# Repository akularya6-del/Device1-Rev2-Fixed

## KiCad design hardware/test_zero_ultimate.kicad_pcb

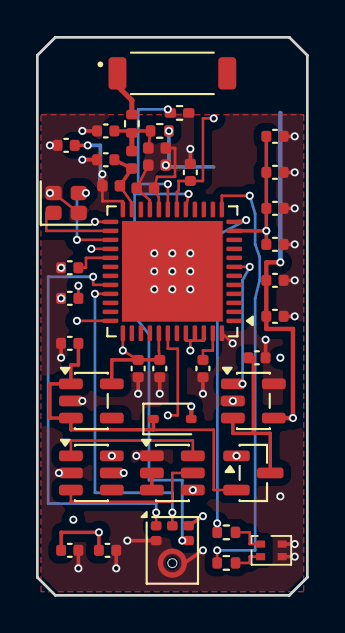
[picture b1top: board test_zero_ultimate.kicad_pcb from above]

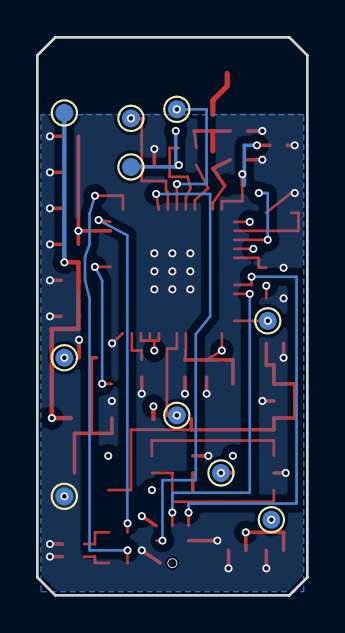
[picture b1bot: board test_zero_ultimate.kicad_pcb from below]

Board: 4 copper layers, 15.0 x 31.0 mm, 50 parts (10 on the bottom side), 33 nets.

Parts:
ANT1: 0868AT43A0020E; Johanson_0868AT43A0020E_CUSTOM
C1, C2, C3, C4, C5, C7, C8, C9, C10, C11, C12, C13, C14, C15, C16, C17, C18, C20, C21: C_0402_1005Metric
C22, C23: 1.5pF; C_0402_1005Metric
D1: D_SOD-323
D2: LED_LiteOn_LTST-C295K_1.6x0.8mm
L1: L_0402_1005Metric
L2: 47nH; L_0402_1005Metric
L3: 18nH; L_0402_1005Metric
MK1: Knowles_SPH0645LM4H-6_3.5x2.65mm
Q1: SOT-23-6
Q2: SOT-23
R1, R6, R7: R_0402_1005Metric
R_ANT: R_0402_1005Metric
R_TEST: R_0402_1005Metric
TP_3V3: TestPoint_Pad_D1.0mm
TP_BATT_N: TestPoint_Pad_D1.0mm
TP_BATT_P: TestPoint_Pad_D1.0mm
TP_BOOT0: TestPoint_Pad_D1.0mm
TP_GND: TestPoint_Pad_D1.0mm
TP_NRST: TestPoint_Pad_D1.0mm
TP_RF: TestPoint_Pad_D1.0mm
TP_SWCLK: TestPoint_Pad_D1.0mm
TP_SWDIO: TestPoint_Pad_D1.0mm
TP_VBUS: TestPoint_Pad_D1.0mm
U1: QFN-48-1EP_7x7mm_P0.5mm_EP5.6x5.6mm
U2, U5: SOT-23-5
U4: SOT-23-6
Y1: Crystal_SMD_2016-4Pin_2.0x1.6mm

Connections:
/3V3: C1.1, C2.1, C3.1, C5.1, C8.1, C15.1, C16.1, C20.1, C21.1, MK1.5, TP_3V3.1, U1.11, U1.25, U1.28, U1.37, U1.41, U1.44, U1.45, U1.46, U5.5
/ANT_FEED: ANT1.1, R_ANT.2
/BATT_NEG: Q1.4, TP_BATT_N.1, U4.6
/BATT_POS: TP_BATT_P.1, U4.5
/BOOT0: R1.1, TP_BOOT0.1, U1.19
/CHG_STAT: U1.7, U2.1
/GATE_OC: Q1.5, U4.3
/GATE_OD: Q1.6, U4.1
/GND: C1.2, C2.2, C3.2, C4.2, C5.2, C7.2, C8.2, C9.2, C10.2, C11.2, C12.2, C13.2, C14.2, C15.2, C16.2, C17.2, C18.2, C20.2, C21.2, C23.2, D2.3, D2.4, MK1.2, MK1.3, Q1.1, R1.2, TP_GND.1, U1.48, U1.49, U2.2, U2.5, U4.2, U5.2, Y1.2, Y1.4
/LED_B: D2.2, R7.2
/LED_B_DRV: R7.1, U1.13
/LED_R: D2.1, R6.2
/LED_R_DRV: R6.1, U1.12
/MIC_SCK: MK1.4, U1.17
/MIC_SD: MK1.6, U1.33
/MIC_WS: MK1.1, U1.32
/NRST: C11.1, TP_NRST.1, U1.18
/OSC_IN: U1.26, Y1.1
/OSC_OUT: U1.27, Y1.3
/RFI_N: C23.1, L3.1, U1.21
/RFI_P: C22.2, L3.2, U1.20
/RFO_HP: C13.1, L1.1, L2.2, U1.23
/RF_50OHM: C14.1, C22.1, L1.2, R_ANT.1, R_TEST.1
/SWCLK: TP_SWCLK.1, U1.42
/SWDIO: TP_SWDIO.1, U1.36
/SYS_PWR: C9.1, D1.1, Q2.2, U5.1, U5.3
/TP_RF: R_TEST.2, TP_RF.1
/VBAT_PROT: C17.1, Q2.3, U2.3
/VBUS_5V: C10.1, C18.1, D1.2, Q2.1, TP_VBUS.1, U2.4
/VDDRF1V55: C7.1, U1.29
/VLXSMPS: C12.1, U1.47
/VR_PA: C4.1, L2.1, U1.24
unnamed: Q1.2, Q1.3

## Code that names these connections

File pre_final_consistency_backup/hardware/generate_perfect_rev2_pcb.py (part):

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        ("R_TEST", "Resistor_SMD", "R_0402_1005Metric", 6.8, 5.2, 0),   # Pad 1 faces left at X=6.29
        
        # Local Decoupling & Config Passives
        ("C4",  "Capacitor_SMD", "C_0402_1005Metric", 1.6, 6.0, 180),  # VR_PA Pin 24
        ("R1",  "Resistor_SMD",  "R_0402_1005Metric", 8.8, 7.0, 0),    # BOOT0 Pin 19
        ("C11", "Capacitor_SMD", "C_0402_1005Metric", 11.0, 7.0, 0),   # NRST Pin 18
        ("C7",  "Capacitor_SMD", "C_0402_1005Metric", 1.8, 11.8, 180), # VDDRF1V55 Pin 29
        ("C1",  "Capacitor_SMD", "C_0402_1005Metric", 1.8, 13.5, 180), # VDD Pin 28
        ("C9",  "Capacitor_SMD", "C_0402_1005Metric", 1.8, 17.0, 180), # SYS_PWR input cap
        ("C12", "Capacitor_SMD", "C_0402_1005Metric", 9.8, 17.4, 0),   # VLXSMPS Pin 47
        ("C17", "Capacitor_SMD", "C_0402_1005Metric", 12.2, 17.4, 0),  # VBAT_PROT cap
        
        # Right Column Decoupling Caps (rot = 0: Pad 1 faces inward at X=12.72)
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    # -------------------------------------------------------------

    # RF SECTION (F.Cu)
    # RFO_HP: U1 Pin 23 -> L1 Pad 1 -> C13 Pad 1
    rfo_net = nets["RFO_HP"]
    u1_23 = get_pad_pos("U1", "23")
    l1_1  = get_pad_pos("L1", "1")
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    add_via(tp_rf[0], tp_rf[1], tprf_net)
    route_points([r_tst2, (7.0, 5.2), tp_rf], pcbnew.F_Cu, tprf_net, 0.20)

    # VR_PA: U1 Pin 24 -> C4 Pad 1
    vrpa_net = nets["VR_PA"]
    u1_24 = get_pad_pos("U1", "24")
    c4_1  = get_pad_pos("C4", "1")
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    route_points([c11_1, (10.52, 6.2), tp_nr], pcbnew.F_Cu, nrst_net, 0.15)

    # OSCILLATOR (F.Cu)
    # OSC_IN: U1 Pin 26 to Y1 Pad 1
    osc_in_net = nets["OSC_IN"]
    u1_26 = get_pad_pos("U1", "26")
    y1_1  = get_pad_pos("Y1", "1")
    route_points([u1_26, (3.0, 10.25), (3.0, 9.75), y1_1], pcbnew.F_Cu, osc_in_net, 0.15)

    # OSC_OUT: U1 Pin 27 to Y1 Pad 3
    osc_out_net = nets["OSC_OUT"]
    u1_27 = get_pad_pos("U1", "27")
    y1_3  = get_pad_pos("Y1", "3")
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    c7_1  = get_pad_pos("C7", "1")
    route_points([u1_29, (3.0, 11.75), (3.0, 11.8), c7_1], pcbnew.F_Cu, vddrf_net, 0.20)

    # VLXSMPS: U1 Pin 47 to C12 Pad 1
    vlx_net = nets["VLXSMPS"]
    u1_47 = get_pad_pos("U1", "47")
    c12_1 = get_pad_pos("C12", "1")
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    add_via(tp_clk[0], tp_clk[1], swclk_net)
    add_track(u1_42[0], u1_42[1], tp_clk[0], tp_clk[1], pcbnew.F_Cu, swclk_net, 0.15)

    # CHG_STAT: U1 Pin 7 to U2 Pin 1 (In2.Cu)
    stat_net = nets["CHG_STAT"]
    u1_7 = get_pad_pos("U1", "7")
    u2_1 = get_pad_pos("U2", "1")
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    route_points([(11.4, 12.25), (11.4, 18.2), (10.863, 18.2)], pcbnew.In2_Cu, stat_net, 0.15)

    # AUDIO I2S LINES
    # MIC_WS: U1 Pin 32 to MK1 Pad 1 (In2.Cu at X=0.8)
    mic_ws_net = nets["MIC_WS"]
    u1_32 = get_pad_pos("U1", "32")
    mk1_1 = get_pad_pos("MK1", "1")
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    add_track(5.5, 27.136, mk1_1[0], mk1_1[1], pcbnew.F_Cu, mic_ws_net, 0.15)
    route_points([(2.8, 13.25), (0.8, 13.25), (0.8, 27.136), (5.5, 27.136)], pcbnew.In2_Cu, mic_ws_net, 0.15)

    # MIC_SD: U1 Pin 33 to MK1 Pad 6 (B.Cu at X=0.6)
    mic_sd_net = nets["MIC_SD"]
    u1_33 = get_pad_pos("U1", "33")
    mk1_6 = get_pad_pos("MK1", "6")
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    add_track(7.5, 26.2, mk1_6[0], mk1_6[1], pcbnew.F_Cu, mic_sd_net, 0.15)
    route_points([(2.0, 14.5), (0.6, 14.5), (0.6, 26.2), (7.5, 26.2)], pcbnew.B_Cu, mic_sd_net, 0.15)

    # MIC_SCK: U1 Pin 17 to MK1 Pad 4 (B.Cu at X=12.0)
    mic_sck_net = nets["MIC_SCK"]
    u1_17 = get_pad_pos("U1", "17")
    mk1_4 = get_pad_pos("MK1", "4")
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    route_points([(8.25, 7.8), (8.25, 4.8), (12.0, 4.8), (12.0, 26.5), (8.4, 26.5)], pcbnew.B_Cu, mic_sck_net, 0.15)

    # UI LED ROUTING
    # LED_R_DRV: U1 Pin 12 to R6 Pad 1 (In2.Cu at X=11.6)
    led_r_drv = nets["LED_R_DRV"]
    u1_12 = get_pad_pos("U1", "12")
    r6_1  = get_pad_pos("R6", "1")
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    d2_1 = get_pad_pos("D2", "1")
    route_points([r6_2, (11.8, 27.5), (11.8, 28.15), d2_1], pcbnew.F_Cu, led_r_net, 0.15)

    # LED_B_DRV: U1 Pin 13 to R7 Pad 1 (In2.Cu at X=12.2)
    led_b_drv = nets["LED_B_DRV"]
    u1_13 = get_pad_pos("U1", "13")
    r7_1  = get_pad_pos("R7", "1")
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    route_points([r7_2, (11.8, 29.2), (11.8, 28.85), d2_2], pcbnew.F_Cu, led_b_net, 0.15)

    # BATTERY & PROTECTION
    # BATT_POS: TP_BATT_P (4.5, 26.5) to U4 Pin 5 (4.138, 24.0)
    batt_pos_net = nets["BATT_POS"]
    tp_bp = get_pad_pos("TP_BATT_P", "1")
    u4_5  = get_pad_pos("U4", "5")
    add_via(tp_bp[0], tp_bp[1], batt_pos_net)
    route_points([tp_bp, (4.138, 26.5), u4_5], pcbnew.F_Cu, batt_pos_net, 0.25)

    # BATT_NEG: TP_BATT_N (2.0, 26.5) to U4 Pin 6 & Q1 Pin 4
    batt_neg_net = nets["BATT_NEG"]
    tp_bn = get_pad_pos("TP_BATT_N", "1")
    u4_6  = get_pad_pos("U4", "6")
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    add_track(8.637, 26.0, q1_4[0], q1_4[1], pcbnew.F_Cu, batt_neg_net, 0.30)
    route_points([tp_bn, (8.637, 26.5), (8.637, 26.0)], pcbnew.B_Cu, batt_neg_net, 0.30)

    # GATE_OD: U4 Pin 1 to Q1 Pin 6 (In2.Cu at Y=22.8)
    od_net = nets["GATE_OD"]
    u4_1 = get_pad_pos("U4", "1")
    q1_6 = get_pad_pos("Q1", "6")
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    add_track(8.637, 22.2, q1_6[0], q1_6[1], pcbnew.F_Cu, od_net, 0.15)
    add_track(1.863, 22.2, 8.637, 22.2, pcbnew.In2_Cu, od_net, 0.15)

    # GATE_OC: U4 Pin 3 to Q1 Pin 5 (In2.Cu at Y=25.2)
    oc_net = nets["GATE_OC"]
    u4_3 = get_pad_pos("U4", "3")
    q1_5 = get_pad_pos("Q1", "5")
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
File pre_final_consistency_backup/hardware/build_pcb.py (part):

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    add_track(4.65, 3.490, 4.65, 2.000, pcbnew.F_Cu, nets["ANT_FEED"], 0.29)

    # 8. Crystal HSE 32MHz (Low parasitic direct connections)
    # U1 Pin 26 (OSC_IN: 4.062, 10.250) to Y1 Pad 1 (1.30, 13.050)
    add_track(4.062, 10.250, 2.8, 10.250, pcbnew.F_Cu, nets["OSC_IN"], 0.20)
    add_track(2.8, 10.250, 1.30, 11.750, pcbnew.F_Cu, nets["OSC_IN"], 0.20)
    add_track(1.30, 11.750, 1.30, 13.050, pcbnew.F_Cu, nets["OSC_IN"], 0.20)

    # U1 Pin 27 (OSC_OUT: 4.062, 10.750) to Y1 Pad 3 (2.70, 11.950)
    add_track(4.062, 10.750, 3.2, 10.750, pcbnew.F_Cu, nets["OSC_OUT"], 0.20)
    add_track(3.2, 10.750, 2.70, 11.250, pcbnew.F_Cu, nets["OSC_OUT"], 0.20)
    add_track(2.70, 11.250, 2.70, 11.950, pcbnew.F_Cu, nets["OSC_OUT"], 0.20)

    # 9. Audio I2S Routing
    # MK1 Pad 1 (MIC_WS) at (6.600, 27.436) to U1 Pin 32 at (4.062, 13.250)
    # Via near MK1 to B.Cu, route along bottom, via near U1
    add_track(6.600, 27.436, 6.600, 26.5, pcbnew.F_Cu, nets["MIC_WS"], 0.15)
    add_via(6.600, 26.5, nets["MIC_WS"])
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    add_track(3.0, 14.0, 3.3, 13.250, pcbnew.F_Cu, nets["MIC_WS"], 0.15)
    add_track(3.3, 13.250, 4.062, 13.250, pcbnew.F_Cu, nets["MIC_WS"], 0.15)

    # MK1 Pad 4 (MIC_SCK) at (8.400, 28.258) to U1 Pin 17 at (8.250, 9.062)
    add_track(8.400, 28.258, 8.400, 26.8, pcbnew.F_Cu, nets["MIC_SCK"], 0.15)
    add_via(8.400, 26.8, nets["MIC_SCK"])
    add_track(8.400, 26.8, 8.250, 10.2, pcbnew.B_Cu, nets["MIC_SCK"], 0.15)
    add_via(8.250, 10.2, nets["MIC_SCK"])
    add_track(8.250, 10.2, 8.250, 9.062, pcbnew.F_Cu, nets["MIC_SCK"], 0.15)

    # MK1 Pad 6 (MIC_SD) at (7.500, 27.436) to U1 Pin 33 at (4.062, 13.750)
    add_track(7.500, 27.436, 7.500, 26.5, pcbnew.F_Cu, nets["MIC_SD"], 0.15)
    add_via(7.500, 26.5, nets["MIC_SD"])
    add_track(7.500, 26.5, 3.4, 22.4, pcbnew.B_Cu, nets["MIC_SD"], 0.15)
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    add_track(7.250, 16.5, 3.5, 14.0, pcbnew.B_Cu, nets["SWCLK"], 0.20)

    # 12. UI LED Lines
    # U1 Pin 12 (LED_R: 10.938, 9.750) to R6 Pad 1 (10.2, 26.7)
    add_track(10.938, 9.750, 11.5, 9.750, pcbnew.F_Cu, nets["LED_R"], 0.15)
    add_via(11.5, 9.750, nets["LED_R"])
    add_track(11.5, 9.750, 10.2, 26.0, pcbnew.B_Cu, nets["LED_R"], 0.15)
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    # R6 Pad 2 to D2 Pad 1 (11.7, 28.8)
    add_track(10.2, 27.7, 11.7, 28.8, pcbnew.F_Cu, nets["LED_R"], 0.20)

    # U1 Pin 13 (LED_B: 10.250, 9.062) to R7 Pad 1 (10.2, 28.5)
    add_track(10.250, 9.062, 10.250, 8.5, pcbnew.F_Cu, nets["LED_B"], 0.15)
    add_via(10.250, 8.5, nets["LED_B"])
    add_track(10.250, 8.5, 10.2, 28.0, pcbnew.B_Cu, nets["LED_B"], 0.15)
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    add_track(10.9, 21.75, 4.1, 24.7, pcbnew.B_Cu, nets["VBAT_PROT"], 0.25)
    add_via(4.1, 24.7, nets["VBAT_PROT"])

    # SYS_PWR: Q2 Pad 2 (11.0, 25.65), U5 Pad 1 (1.8, 19.85), U5 Pad 3 (1.8, 21.75), C20 Pad 1 (6.0, 21.28), C9 Pad 1 (7.0, 17.5), C10 Pad 1 (10.0, 17.5), U1 Pin 24 (4.750, 9.062)
    add_track(1.8, 19.85, 1.8, 21.75, pcbnew.F_Cu, nets["SYS_PWR"], 0.35)
    add_track(1.8, 21.75, 6.0, 21.28, pcbnew.F_Cu, nets["SYS_PWR"], 0.35)
    add_track(6.0, 21.28, 11.0, 25.65, pcbnew.F_Cu, nets["SYS_PWR"], 0.35)
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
